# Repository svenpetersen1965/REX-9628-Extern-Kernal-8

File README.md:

# REX-9628-Extern-Kernal-8
This is the reverse engineering of the REX Datentechnik 9628 Extern Kernal 8 for the Commodore C64. The components date back to 1988. So does the design.

The reverse engineering was conducted in order to learn about the functions of a kernal cartridge for the C64. 

The original Extern Kernal 8 is working. The design included in this repository is declared to be untested, the files are offered for educational purposes only.  
# Calculation
The BOM value is 11.41€ (two 27c256 for 2€ each included). The shipping costs for the components are not included in the calculation

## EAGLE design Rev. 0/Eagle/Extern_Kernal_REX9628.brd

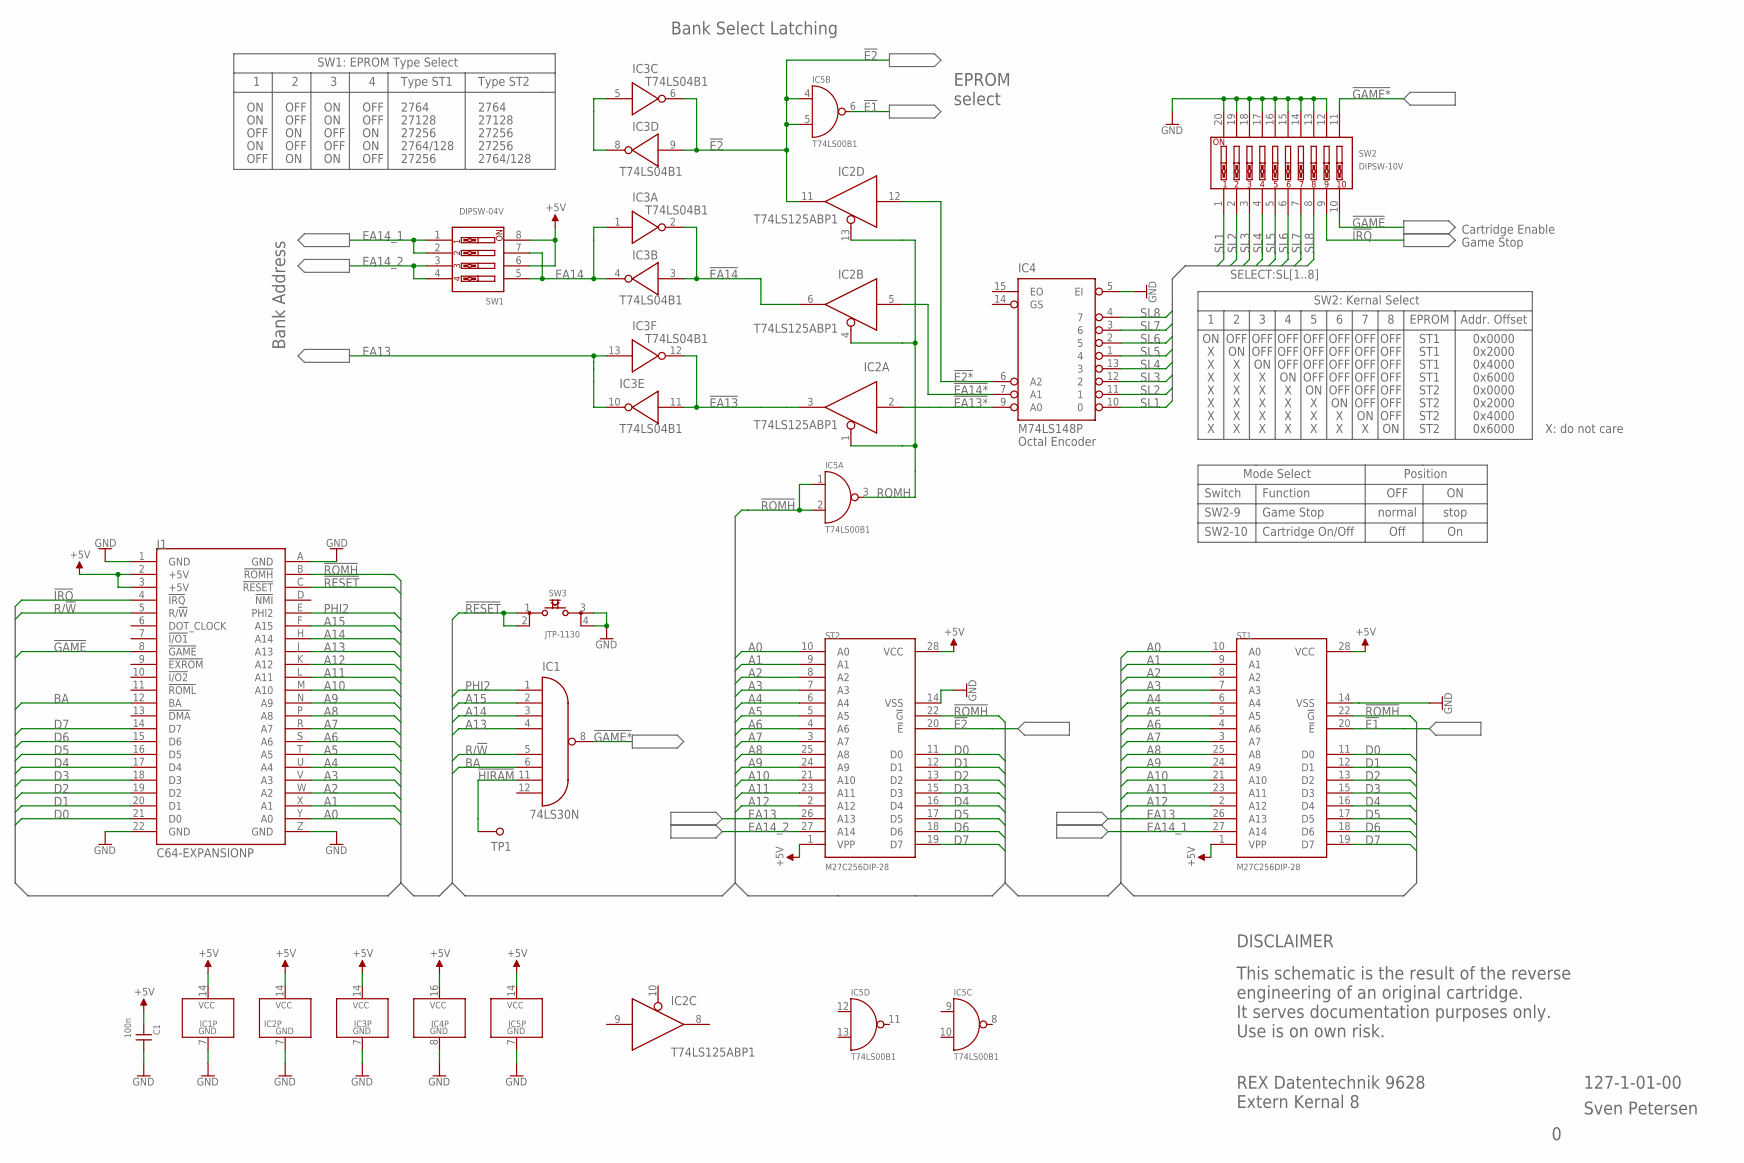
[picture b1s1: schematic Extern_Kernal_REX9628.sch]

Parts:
C1: 100n; C-2,5
IC1: 74LS30N; DIL-14
IC2: T74LS125ABP1; DIL-14
IC3: T74LS04B1; DIL-14
IC4: M74LS148P; DIL-16
IC5: T74LS00B1; DIL-14
J1: C64-EXPANSIONP; EXPPORT
ST1, ST2: M27C256DIP-28; DIL28-6
SW1: DIPSW-04V
SW2: DIPSW-10V
SW3: JTP-1130
TP1: 1,3/2,0

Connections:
!E1: IC5.6 (O), ST1.20 (!E)
!E2: IC2.11 (O), IC3.6 (O), IC3.9 (I), IC5.4 (I0), IC5.5 (I1), ST2.20 (!E)
!E2*: IC2.12 (I), IC4.6 (A2)
!EA13: IC2.3 (O), IC3.11 (I), IC3.12 (O)
!EA13*: IC2.2 (I), IC4.9 (A0)
!EA14: IC2.6 (O), IC3.2 (O), IC3.3 (I)
!EA14*: IC2.5 (I), IC4.7 (A1)
!GAME: J1.8 (!GAME), SW2.10
!GAME*: IC1.8 (O), SW2.11
!HIRAM: IC1.11 (I6), TP1.1
!IRQ: J1.4 (!IRQ), SW2.9
!RESET: J1.C (!RESET), SW3.1, SW3.2
!ROMH: IC5.1 (I0), IC5.2 (I1), J1.B (!ROMH), ST1.22 (!G), ST2.22 (!G)
+5V: C1.1, IC1.14 (VCC), IC2.14 (VCC), IC3.14 (VCC), IC4.16 (VCC), IC5.14 (VCC), J1.2 (+5V), J1.3 (+5V), ST1.1 (VPP), ST1.28 (VCC), ST2.1 (VPP), ST2.28 (VCC), SW1.6, SW1.8
A0: J1.Y (A0), ST1.10 (A0), ST2.10 (A0)
A1: J1.X (A1), ST1.9 (A1), ST2.9 (A1)
A2: J1.W (A2), ST1.8 (A2), ST2.8 (A2)
A3: J1.V (A3), ST1.7 (A3), ST2.7 (A3)
A4: J1.U (A4), ST1.6 (A4), ST2.6 (A4)
A5: J1.T (A5), ST1.5 (A5), ST2.5 (A5)
A6: J1.S (A6), ST1.4 (A6), ST2.4 (A6)
A7: J1.R (A7), ST1.3 (A7), ST2.3 (A7)
A8: J1.P (A8), ST1.25 (A8), ST2.25 (A8)
A9: J1.N (A9), ST1.24 (A9), ST2.24 (A9)
A10: J1.M (A10), ST1.21 (A10), ST2.21 (A10)
A11: J1.L (A11), ST1.23 (A11), ST2.23 (A11)
A12: J1.K (A12), ST1.2 (A12), ST2.2 (A12)
A13: IC1.4 (I3), J1.J (A13)
A14: IC1.3 (I2), J1.H (A14)
A15: IC1.2 (I1), J1.F (A15)
BA: IC1.6 (I5), J1.12 (BA)
D0: J1.21 (D0), ST1.11 (D0), ST2.11 (D0)
D1: J1.20 (D1), ST1.12 (D1), ST2.12 (D1)
D2: J1.19 (D2), ST1.13 (D2), ST2.13 (D2)
D3: J1.18 (D3), ST1.15 (D3), ST2.15 (D3)
D4: J1.17 (D4), ST1.16 (D4), ST2.16 (D4)
D5: J1.16 (D5), ST1.17 (D5), ST2.17 (D5)
D6: J1.15 (D6), ST1.18 (D6), ST2.18 (D6)
D7: J1.14 (D7), ST1.19 (D7), ST2.19 (D7)
EA13: IC3.10 (O), IC3.13 (I), ST1.26 (A13), ST2.26 (A13)
EA14: IC3.1 (I), IC3.4 (O), SW1.5, SW1.7
EA14_1: ST1.27 (A14), SW1.1, SW1.2
EA14_2: ST2.27 (A14), SW1.3, SW1.4
GND: C1.2, IC1.7 (GND), IC2.7 (GND), IC3.7 (GND), IC4.5 (EI), IC4.8 (GND), IC5.7 (GND), J1.1 (GND), J1.22 (GND), J1.A (GND), J1.Z (GND), ST1.14 (VSS), ST2.14 (VSS), SW2.12, SW2.13, SW2.14, SW2.15, SW2.16, SW2.17, SW2.18, SW2.19, SW2.20, SW3.3, SW3.4
unnamed: IC3.5 (I), IC3.8 (O)
PHI2: IC1.1 (I0), J1.E (PHI2)
R/!W: IC1.5 (I4), J1.5 (R/!W)
ROMH: IC2.1 (OE), IC2.4 (OE), IC2.13 (OE), IC5.3 (O)
SL1: IC4.10 (0), SW2.1
SL2: IC4.11 (1), SW2.2
SL3: IC4.12 (2), SW2.3
SL4: IC4.13 (3), SW2.4
SL5: IC4.1 (4), SW2.5
SL6: IC4.2 (5), SW2.6
SL7: IC4.3 (6), SW2.7
SL8: IC4.4 (7), SW2.8

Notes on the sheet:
Bank Address
EPROM select
Cartridge Enable
Game Stop
OFF
Type ST1
Type ST2
2764
27128
27256
2764/128
SW1: EPROM Type Select
Octal Encoder
Bank Select Latching
EPROM
Addr. Offset
SW2: Kernal Select
ST1
ST2
0x0000
0x2000
0x4000
0x6000
SW2-9
normal
stop
SW2-10
Cartridge On/Off
Off
Switch
Function
Position
Mode Select
X: do not care
REX Datentechnik 9628
Extern Kernal 8
127-1-01-00
Sven Petersen
DISCLAIMER
This schematic is the result of the reverse engineering of an original cartridge. It serves documentation purposes only. Use is on own risk.

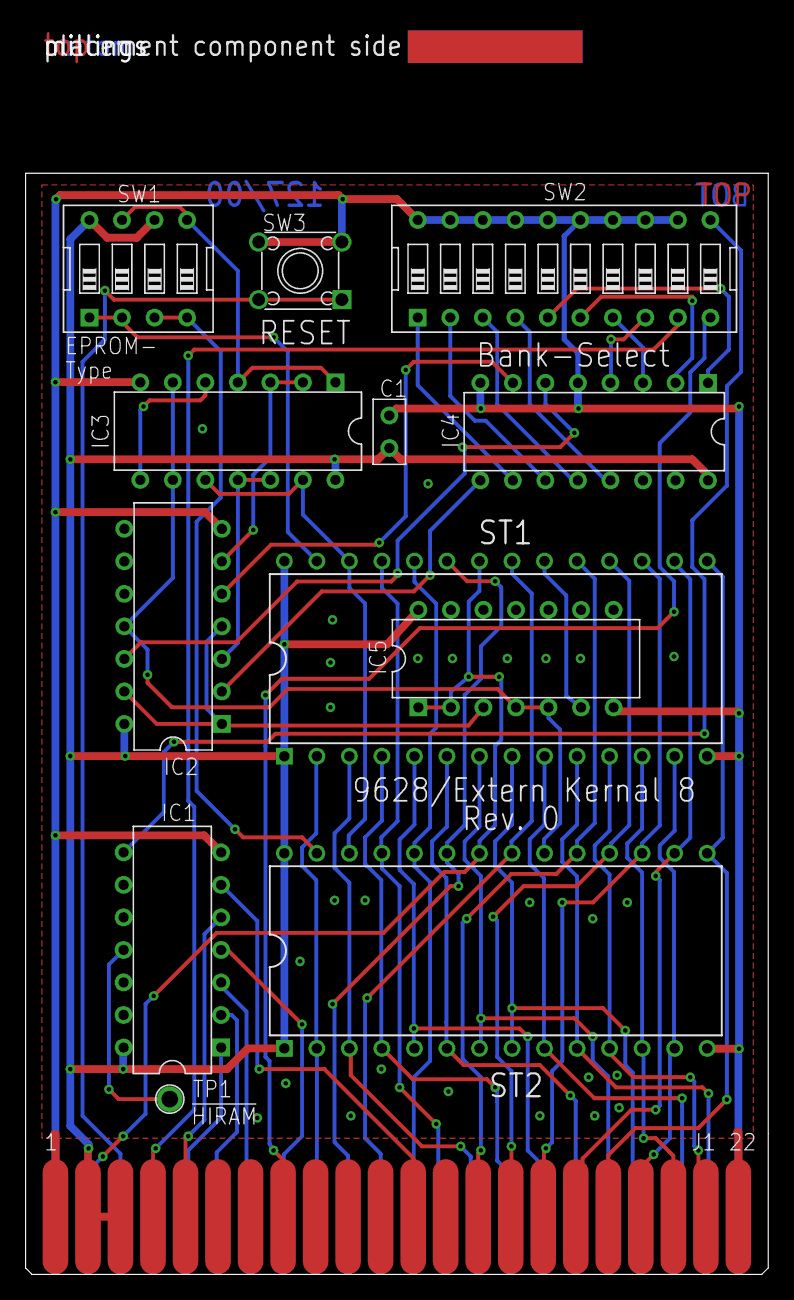
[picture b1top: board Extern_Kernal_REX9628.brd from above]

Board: 2 copper layers, 58.0 x 97.5 mm, 15 parts (0 on the bottom side), 56 nets.

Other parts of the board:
U$44: 2LAYER
U$45: PCB-TITLE/

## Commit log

2019-05-25 Create LICENSE
2020-06-12 BOM calculation added
